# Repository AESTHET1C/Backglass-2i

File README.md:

# Backglass 2 Integrated Pinball Controller Board

This is the "integrated" version of the [Backglass 2 Pinball Controller Board](https://github.com/AESTHET1C/Backglass-2). The I/O has been changed from wire receptacles to a ribbon cable, and the ordering has changed to better suit wire management.

---

An Arduino Uno-compatible unified control board tailored to the Eli Whitney Museum 2019 summer pinball project.

The board contains the following hardware:

* Microchip ATmega8U2/16U2 (serial communication and code upload)
* Microchip ATmega328P (user code)
* Microchip ATmega48PB (audio/visual coprocessing)
* 4-character 7 segment display
* 2 analogue inputs (for reflectance sensors)
* 5 digital inputs (with integrated pull-ups)
* 3 current-limited LED outputs
* 1 PWM-controlled motor output
* 1 speaker output
* Micro USB interface
* 2.7 - 6.5 volt power input

All features of the board, with the exception of the motor, can be powered via USB.

-----

A user-oriented code library can be found here: <https://github.com/AESTHET1C/Backglass-2-Library/>

The coprocessor firmware can be found here: <https://github.com/AESTHET1C/Backglass-2-Firmware/>

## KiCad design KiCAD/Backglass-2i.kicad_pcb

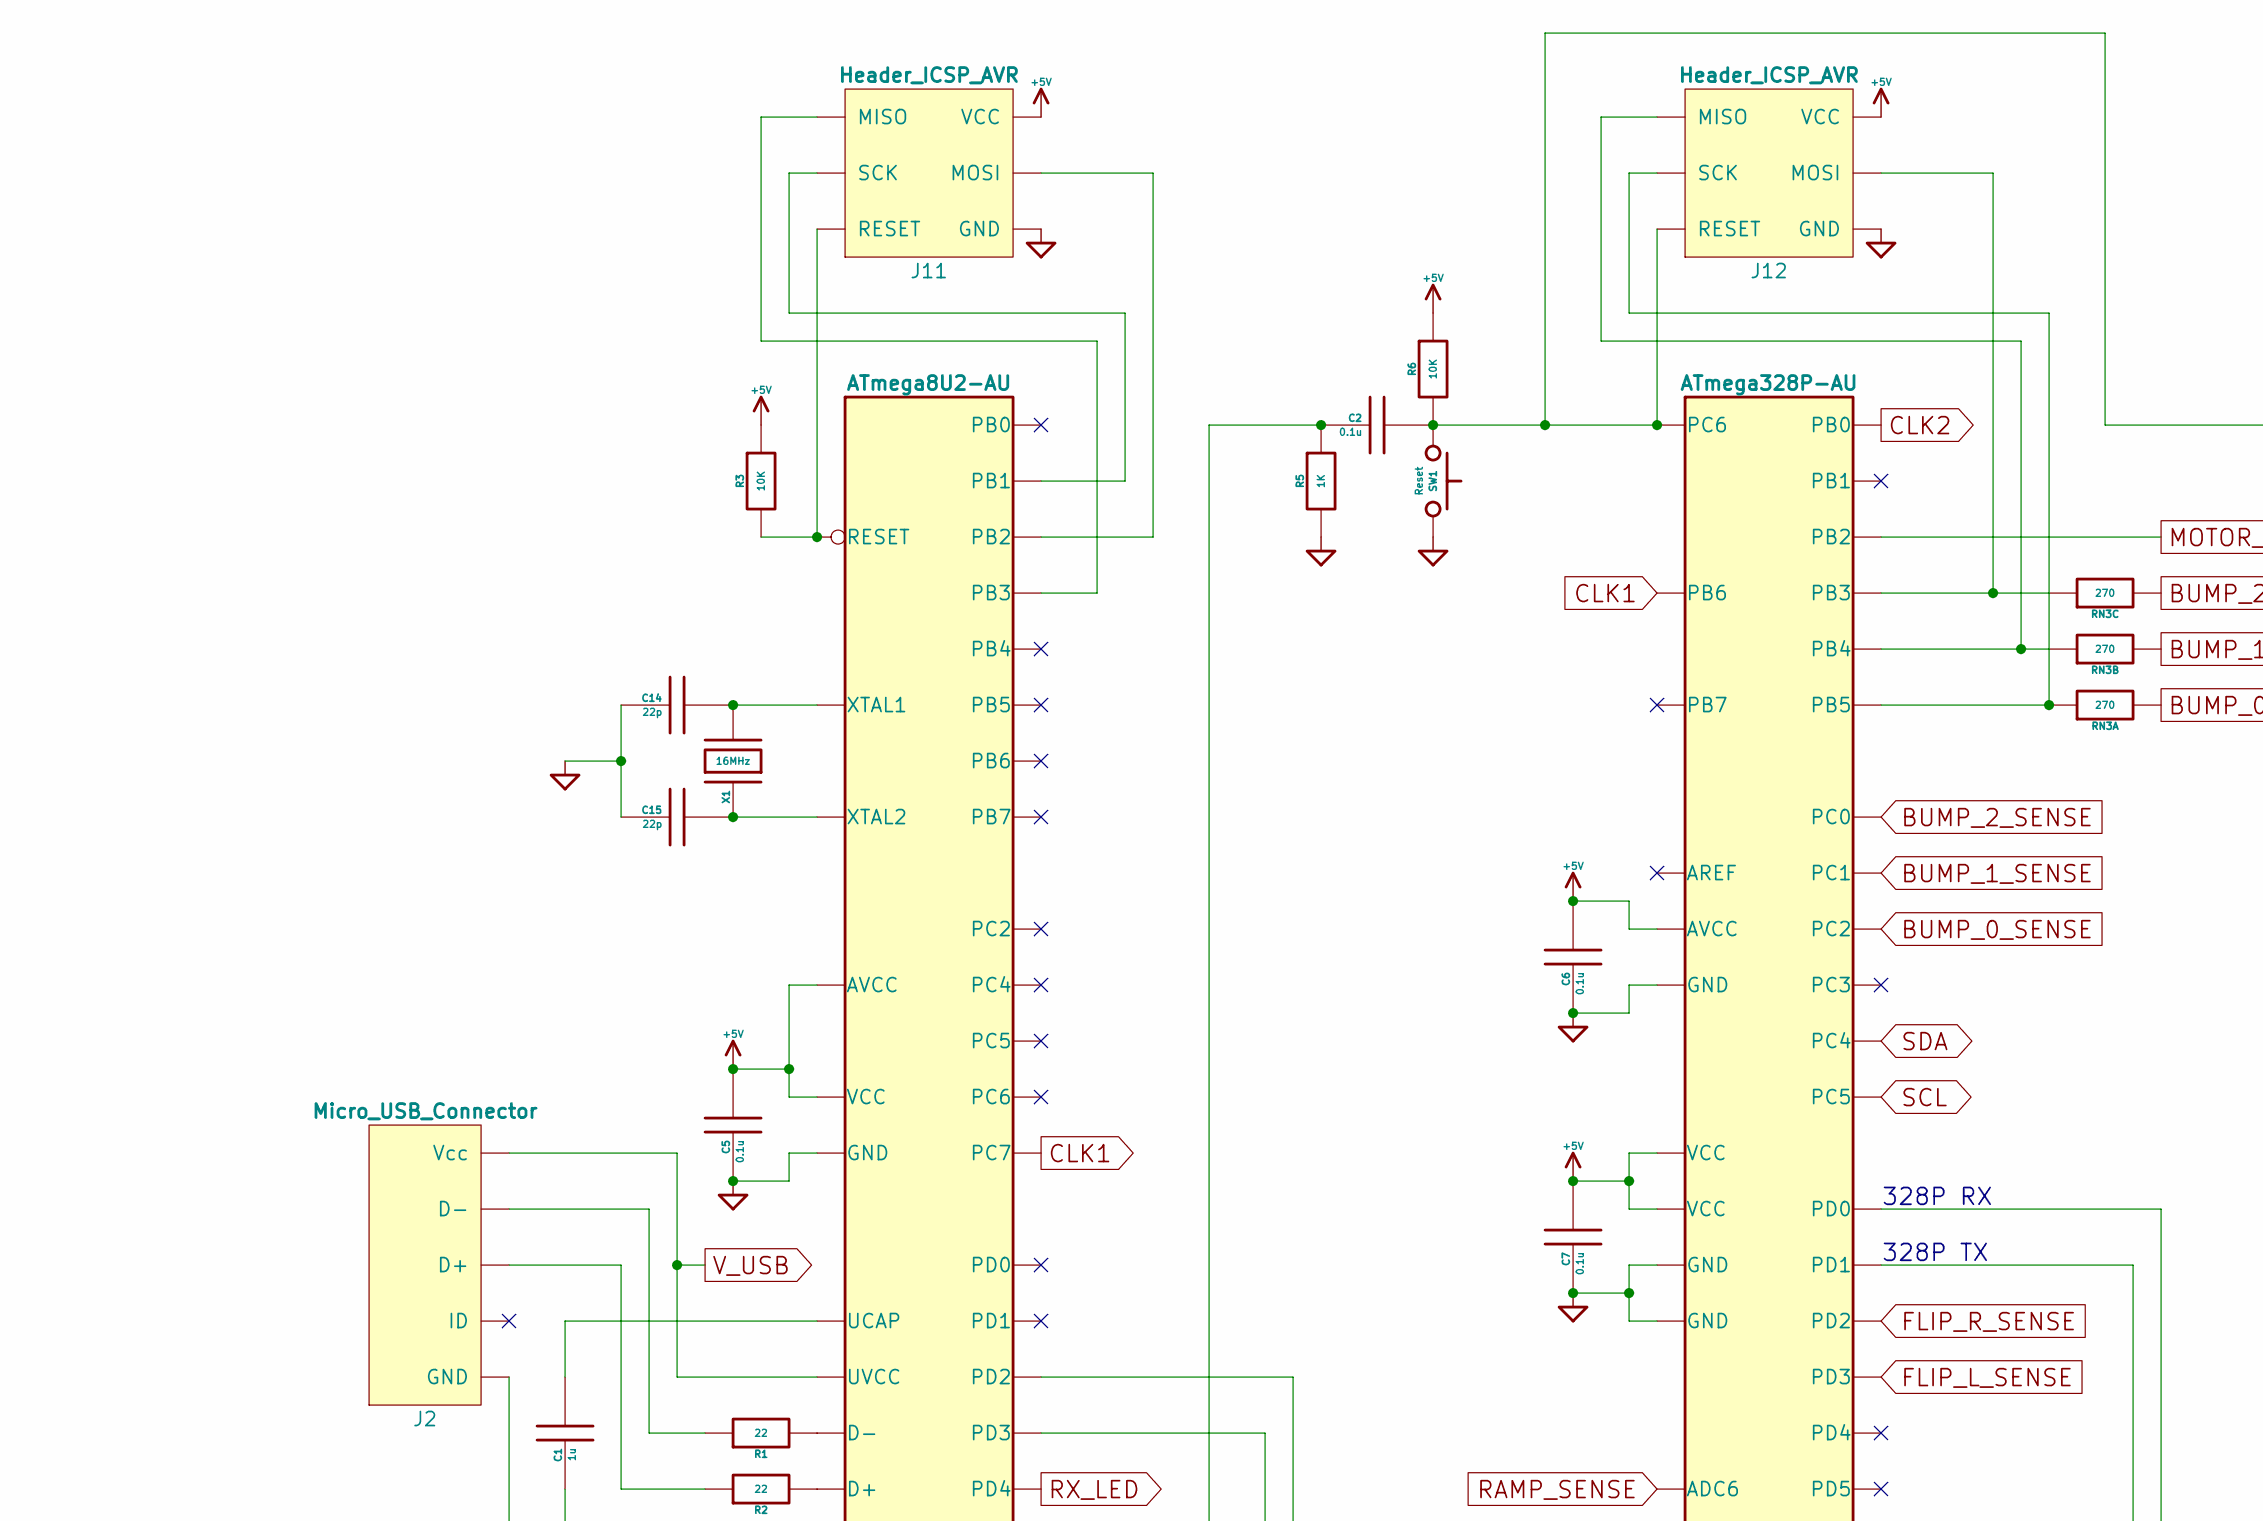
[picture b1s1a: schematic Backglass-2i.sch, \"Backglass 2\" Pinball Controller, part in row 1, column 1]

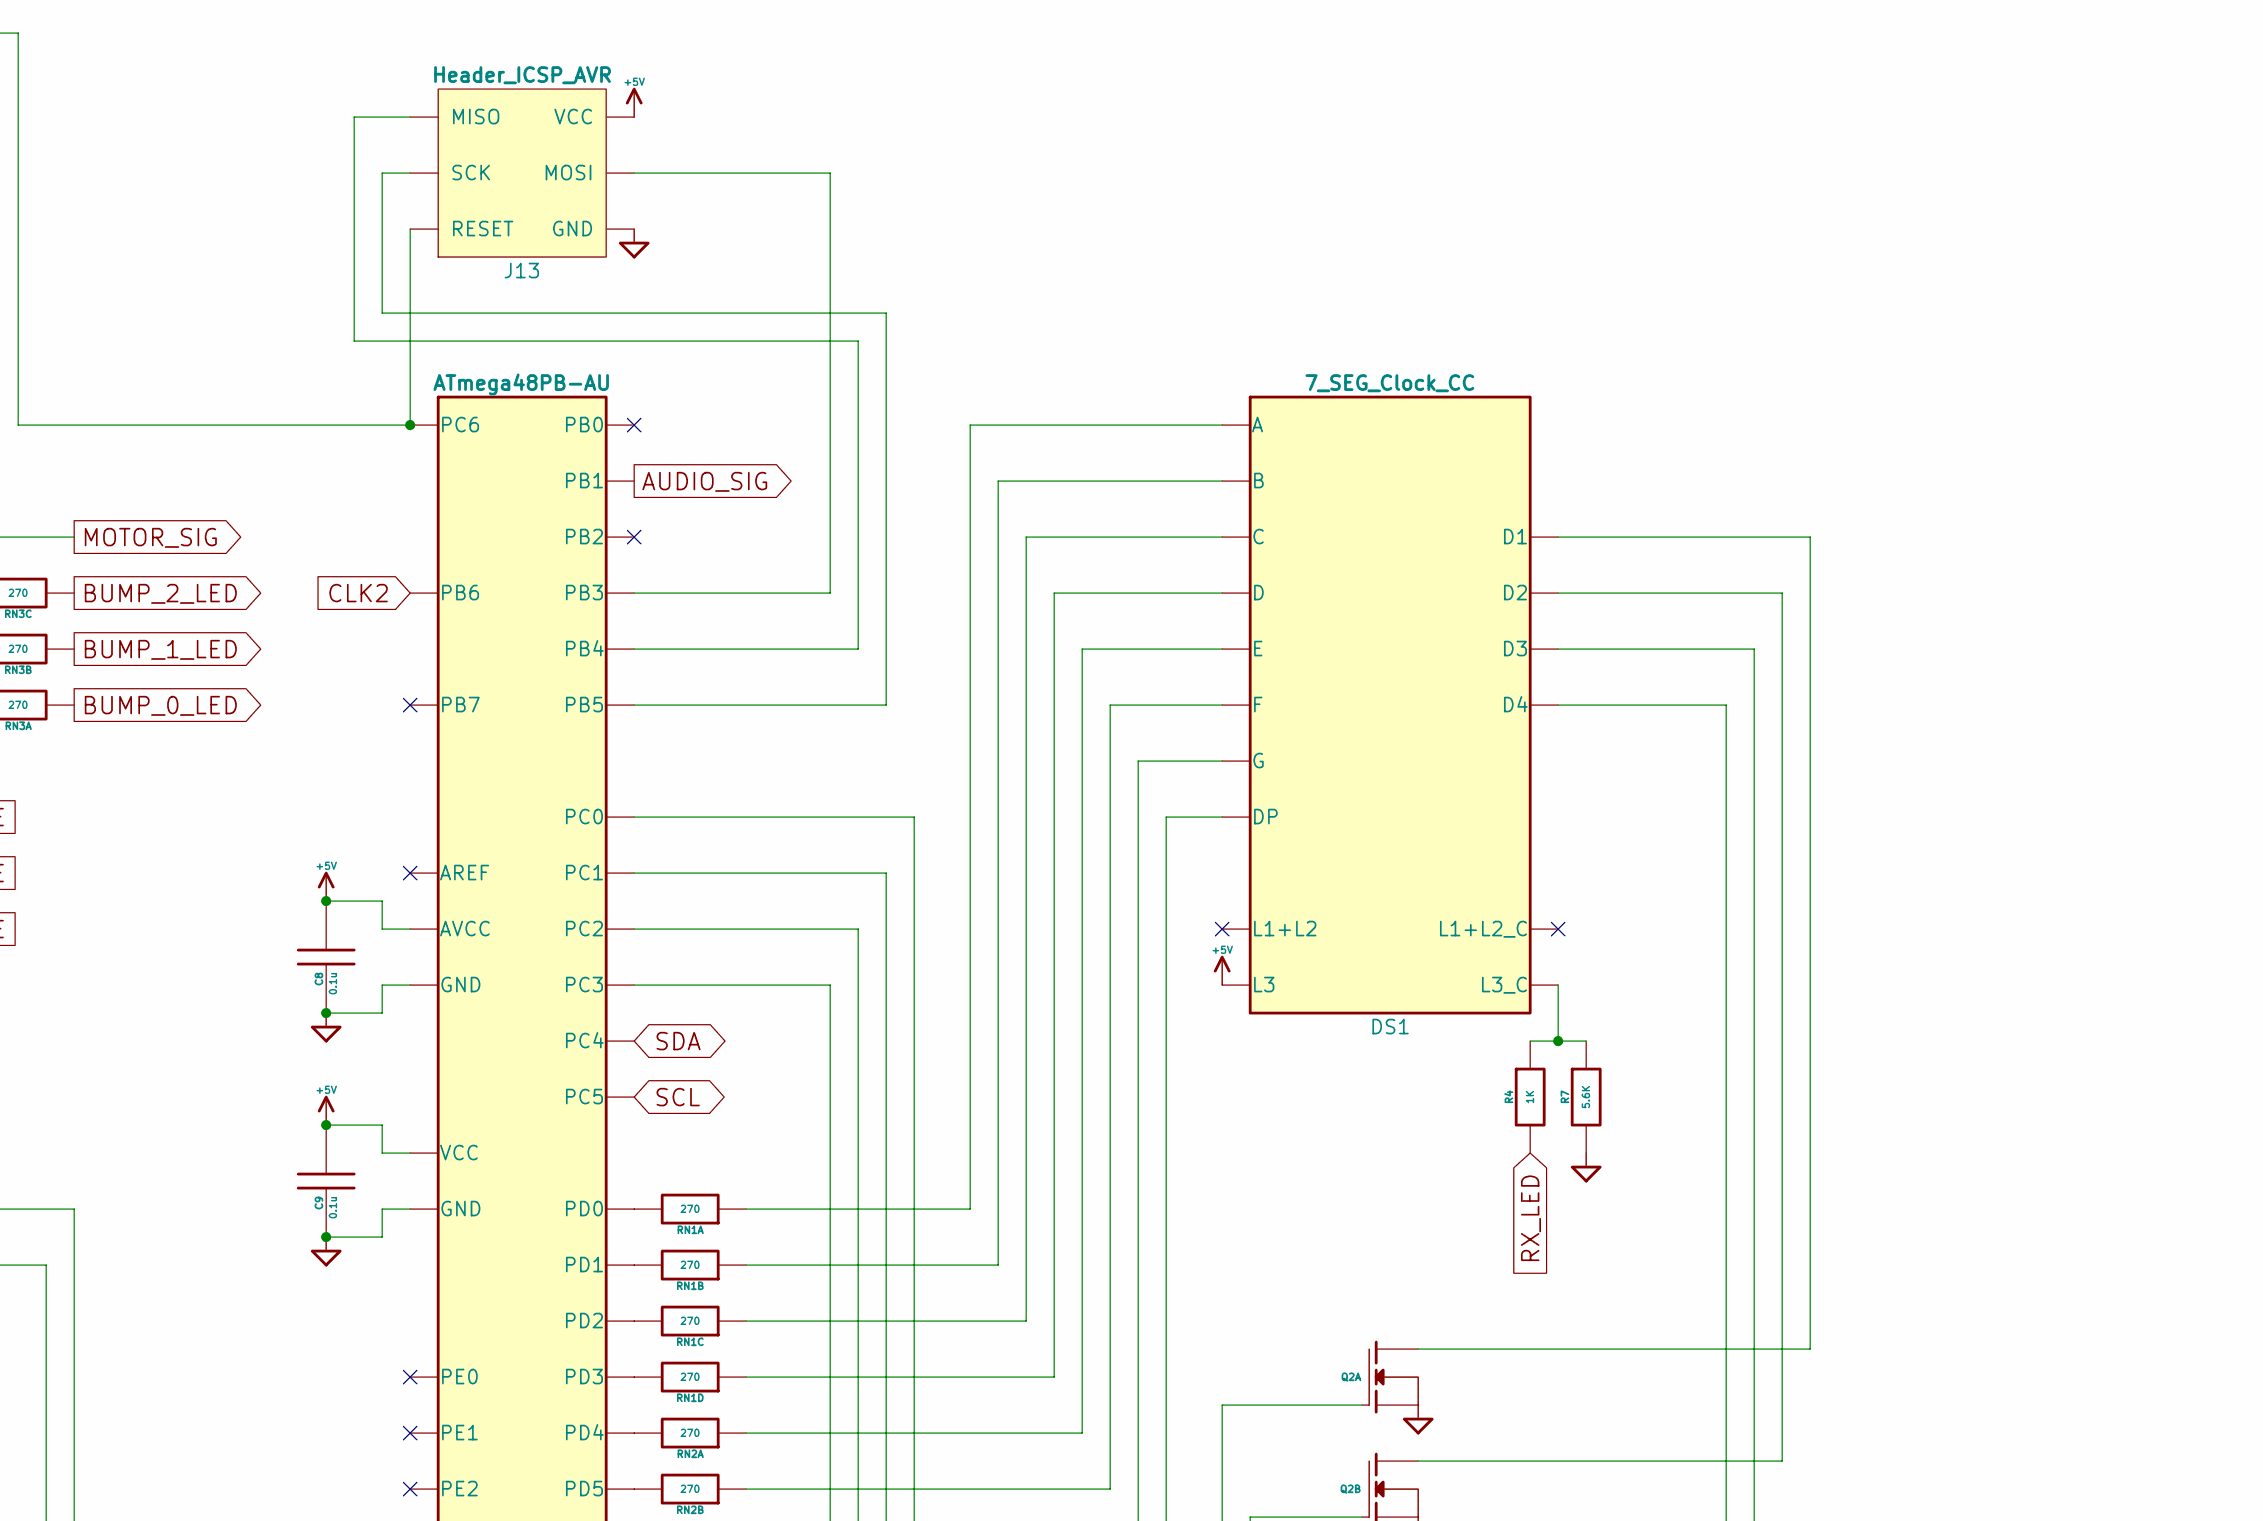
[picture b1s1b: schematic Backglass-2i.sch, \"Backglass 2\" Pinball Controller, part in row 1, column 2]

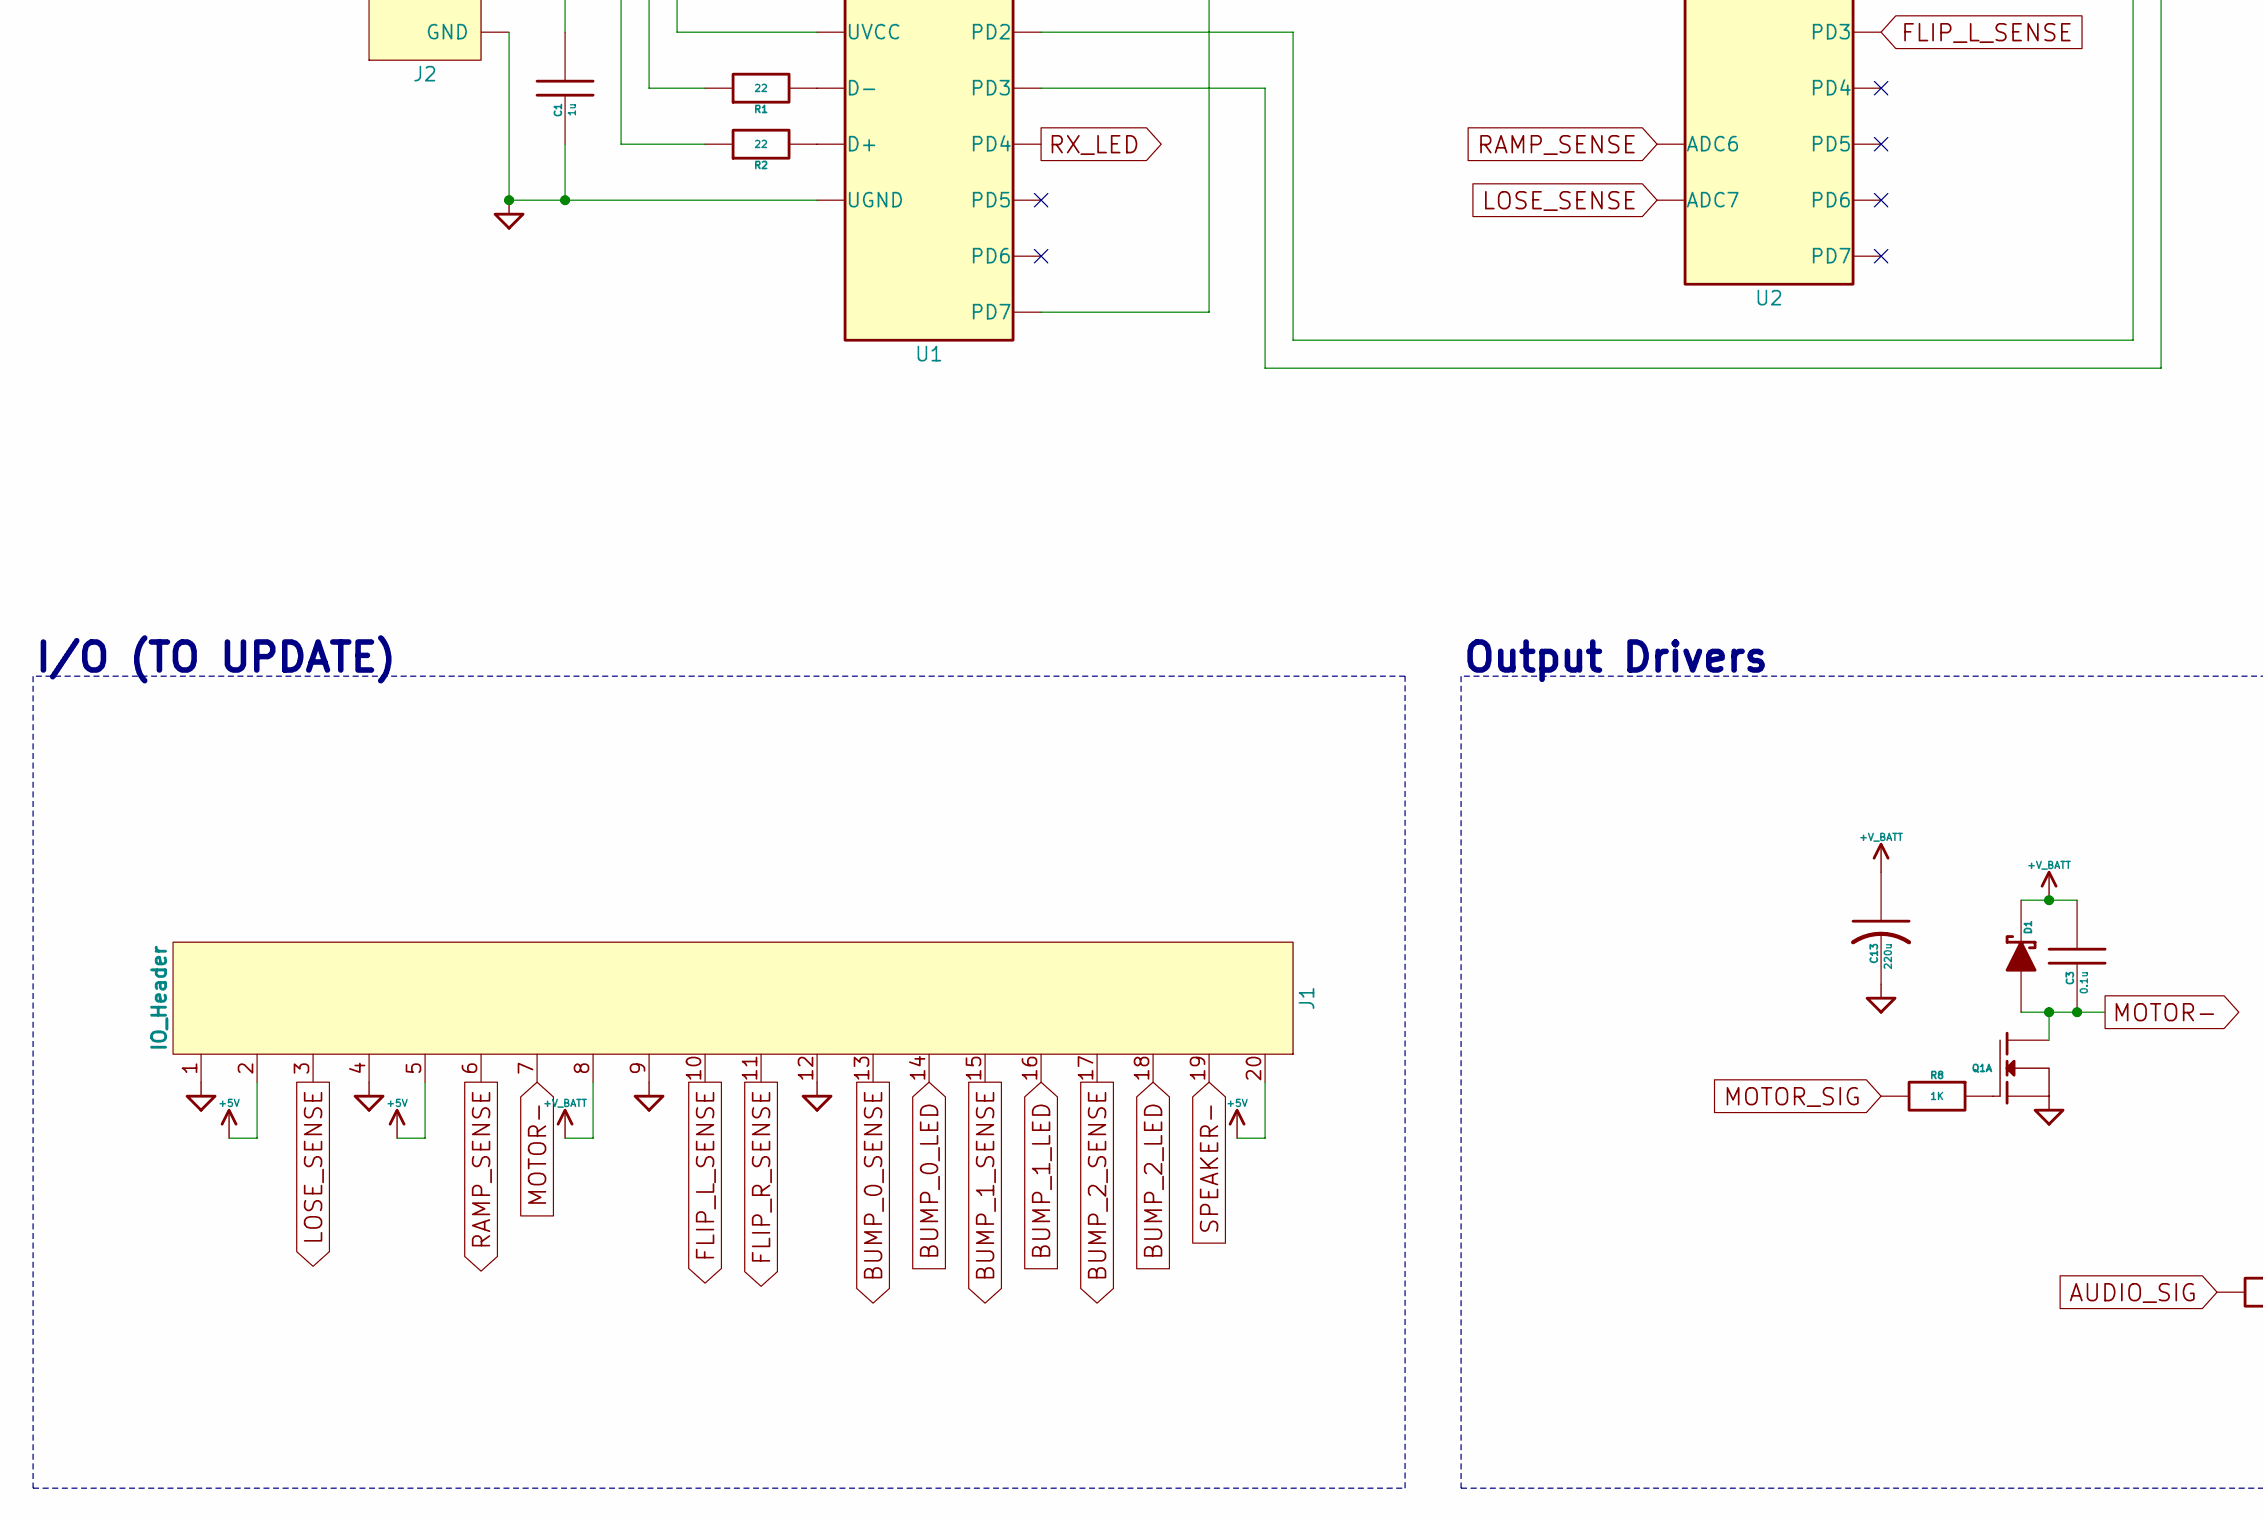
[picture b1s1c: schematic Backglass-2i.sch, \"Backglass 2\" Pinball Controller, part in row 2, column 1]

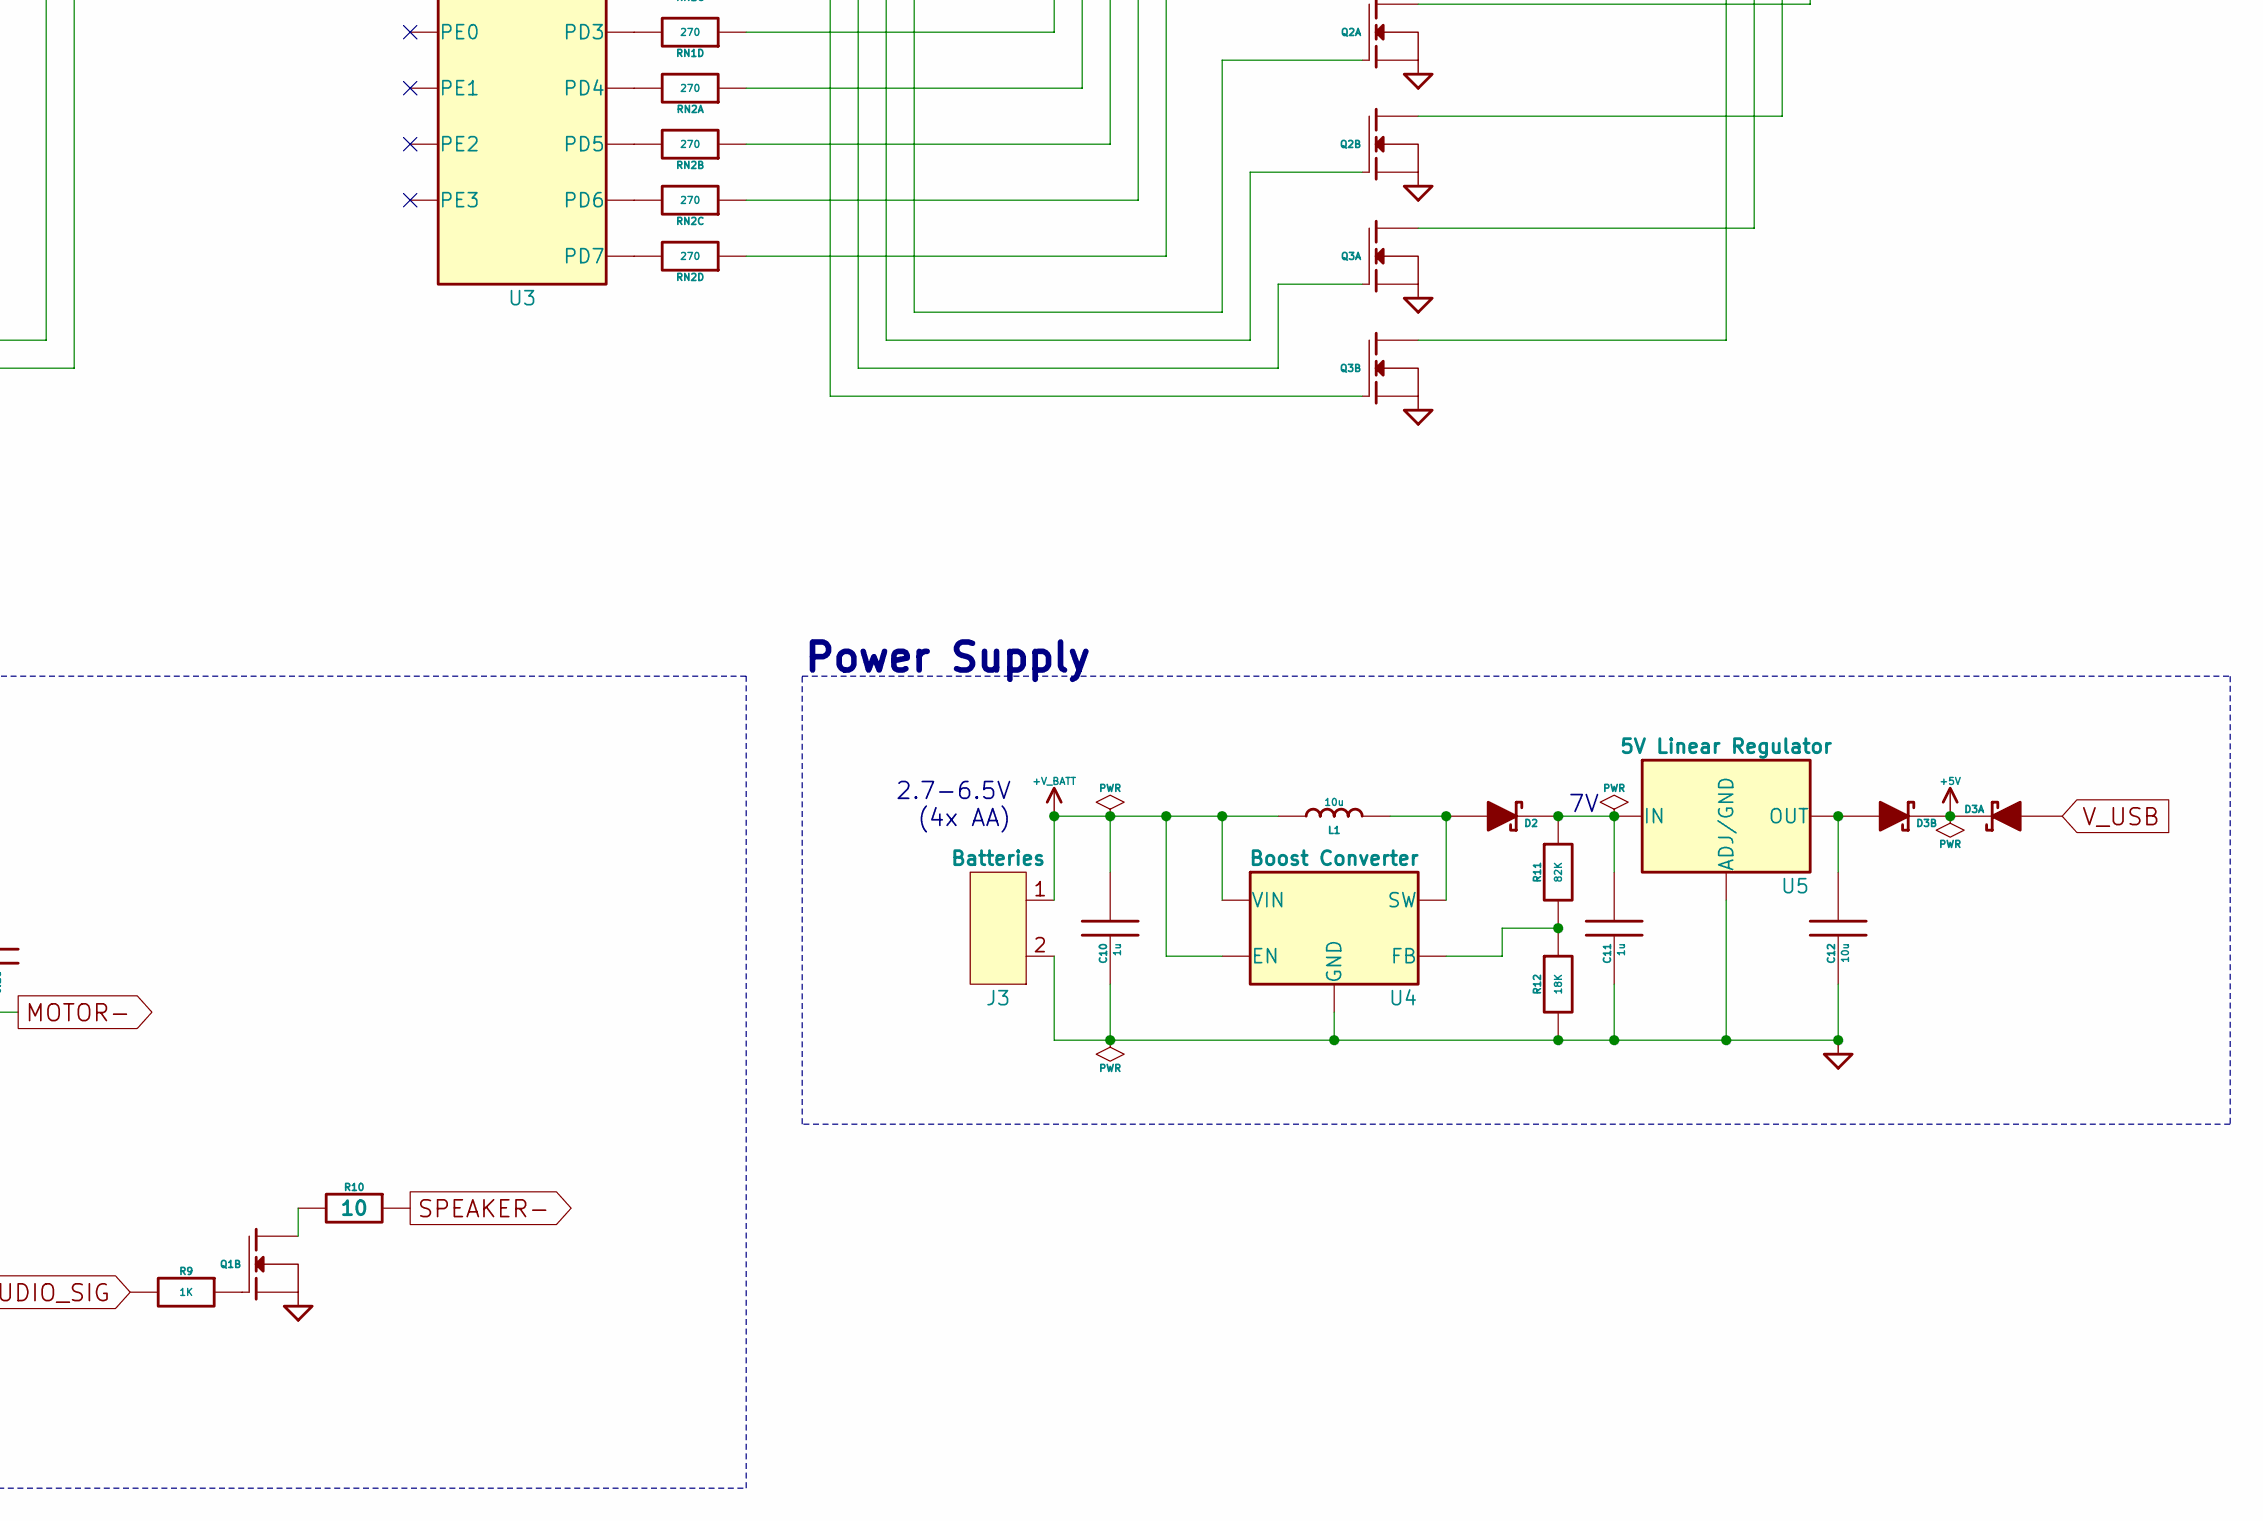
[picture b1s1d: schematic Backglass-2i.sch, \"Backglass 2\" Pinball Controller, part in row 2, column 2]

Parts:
C1, C10, C11: 1u; 1608
C2, C3, C5, C6, C7, C8, C9: 0.1u; 1608
C12: 10u; 2012
C13: 220u; C_6.3-2.5mm
C14, C15: 22p; 1608
D1, D2: D_Schottky; SOT-23-3_A-C
D3: D_Schottky_Dual_CC; SOT-23-3_AAC
DS1: 7_SEG_Clock_CC; TDCx10xxM
J1: IO_Header; TE_1-746610-5
J2: Micro_USB_Connector; Molex_1051640001
J3: Batteries; 2x1_0.1in
J11, J12, J13: Header_ICSP_AVR; AVR_ICSP_0.05in
L1: 10u; 3225
Q1: MOSFET_N_E_Dual; SOT-23-6_G1-S2-G2-D2-S1-D1
Q2, Q3: MOSFET_N_E_Dual; TSSOP-6_S1-G1-D2-S2-G2-D1
R1, R2: 22; 1608
R3, R6: 10K; 1608
R4, R5, R8, R9: 1K; 1608
R7: 5.6K; 1608
R10: 10; 3225
R11: 82K; 1608
R12: 18K; 1608
RN1, RN2, RN3: 270; Array_4x1608_Convex_NP
SW1: Reset; Tact_Switch_6mm
U1: ATmega8U2-AU; TQFP-32
U2: ATmega328P-AU; TQFP-32
U3: ATmega48PB-AU; TQFP-32
U4: Boost Converter; SOT-23-5
U5: 5V Linear Regulator; SOT-223-4
X1: 16MHz; 3.2x2.5_SMD_CRYSTAL

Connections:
+5V: C5.2, C6.2, C7.2, C8.2, C9.2, D3.C, DS1.9 (L3), J1.2, J1.5, J1.20, J11.2 (VCC), J12.2 (VCC), J13.2 (VCC), R3.1, R6.1, U1.4 (VCC), U1.32 (AVCC), U2.4 (VCC), U2.6 (VCC), U2.18 (AVCC), U3.4 (VCC), U3.18 (AVCC)
+V_BATT: C3.2, C10.2, C13.1, D1.C, J1.8, J3.1, L1.1, U4.4 (EN), U4.5 (VIN)
AUDIO_SIG: R9.2, U3.13 (PB1)
BUMP_0_LED: J1.14, RN3.8
BUMP_0_SENSE: J1.13, U2.25 (PC2)
BUMP_1_LED: J1.16, RN3.7
BUMP_1_SENSE: J1.15, U2.24 (PC1)
BUMP_2_LED: J1.18, RN3.6
BUMP_2_SENSE: J1.17, U2.23 (PC0)
CLK1: U1.22 (PC7), U2.7 (PB6)
CLK2: U2.12 (PB0), U3.7 (PB6)
FLIP_L_SENSE: J1.10, U2.1 (PD3)
FLIP_R_SENSE: J1.11, U2.32 (PD2)
GND: C1.1, C5.1, C6.1, C7.1, C8.1, C9.1, C10.1, C11.1, C12.1, C13.2, C14.1, C15.1, J1.1, J1.4, J1.9, J1.12, J2.5 (GND), J3.2, J11.6 (GND), J12.6 (GND), J13.6 (GND), Q1.S1, Q1.S2, Q2.S1, Q2.S2, Q3.S1, Q3.S2, R5.2, R7.2, R12.2, SW1.2 (NO), U1.3 (GND), U1.28 (UGND), U2.3 (GND), U2.5 (GND), U2.21 (GND), U3.5 (GND), U3.21 (GND), U4.2 (GND), U5.1 (ADJ/GND)
LOSE_SENSE: J1.3, U2.22 (ADC7)
MOTOR-: C3.1, D1.A, J1.7, Q1.D1
MOTOR_SIG: R8.2, U2.14 (PB2)
unnamed: C1.2, U1.27 (UCAP)
unnamed: C2.1, R5.1, U1.13 (PD7)
unnamed: C2.2, J12.5 (RESET), J13.5 (RESET), R6.2, SW1.1 (C), U2.29 (PC6), U3.29 (PC6)
unnamed: C11.2, D2.C, R11.1, U5.3 (IN)
unnamed: C12.2, D3.A2, U5.2 (OUT), U5.4
unnamed: C14.2, U1.1 (XTAL1), X1.2
unnamed: C15.2, U1.2 (XTAL2), X1.1
unnamed: D2.A, L1.2, U4.1 (SW)
unnamed: DS1.1 (D1), Q2.D1
unnamed: DS1.2 (D2), Q2.D2
unnamed: DS1.3 (D), RN1.4
unnamed: DS1.5 (E), RN2.1
unnamed: DS1.6 (D3), Q3.D1
unnamed: DS1.7 (DP), RN2.4
unnamed: DS1.8 (D4), Q3.D2
unnamed: DS1.10 (L3_C), R4.1, R7.1
unnamed: DS1.11 (F), RN2.2
unnamed: DS1.13 (C), RN1.3
unnamed: DS1.14 (A), RN1.1
unnamed: DS1.15 (G), RN2.3
unnamed: DS1.16 (B), RN1.2
unnamed: J2.2 (D-), R1.1
unnamed: J2.3 (D+), R2.1
unnamed: J11.1 (MISO), U1.17 (PB3)
unnamed: J11.3 (SCK), U1.15 (PB1)
unnamed: J11.4 (MOSI), U1.16 (PB2)
unnamed: J11.5 (RESET), R3.2, U1.24 (RESET)
unnamed: J12.1 (MISO), RN3.2, U2.16 (PB4)
unnamed: J12.3 (SCK), RN3.1, U2.17 (PB5)
unnamed: J12.4 (MOSI), RN3.3, U2.15 (PB3)
unnamed: J13.1 (MISO), U3.16 (PB4)
unnamed: J13.3 (SCK), U3.17 (PB5)
unnamed: J13.4 (MOSI), U3.15 (PB3)
unnamed: Q1.D2, R10.2
unnamed: Q1.G1, R8.1
unnamed: Q1.G2, R9.1
unnamed: Q2.G1, U3.23 (PC0)
unnamed: Q2.G2, U3.24 (PC1)
unnamed: Q3.G1, U3.25 (PC2)
unnamed: Q3.G2, U3.26 (PC3)
unnamed: R1.2, U1.30 (D-)
unnamed: R2.2, U1.29 (D+)
unnamed: R11.2, R12.1, U4.3 (FB)
unnamed: RN1.5, U3.1 (PD3)
unnamed: RN1.6, U3.32 (PD2)
unnamed: RN1.7, U3.31 (PD1)
unnamed: RN1.8, U3.30 (PD0)
unnamed: RN2.5, U3.11 (PD7)
unnamed: RN2.6, U3.10 (PD6)
unnamed: RN2.7, U3.9 (PD5)
unnamed: RN2.8, U3.2 (PD4)
unnamed: U1.8 (PD2), U2.31 (PD1)
unnamed: U1.9 (PD3), U2.30 (PD0)
RAMP_SENSE: J1.6, U2.19 (ADC6)
RX_LED: R4.2, U1.10 (PD4)
SCL: U2.28 (PC5), U3.28 (PC5)
SDA: U2.27 (PC4), U3.27 (PC4)
SPEAKER-: J1.19, R10.1
V_USB: D3.A1, J2.1 (Vcc), U1.31 (UVCC)

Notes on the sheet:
328P RX
328P TX
2.7-6.5V (4x AA)
Power Supply
I/O (TO UPDATE)
Output Drivers

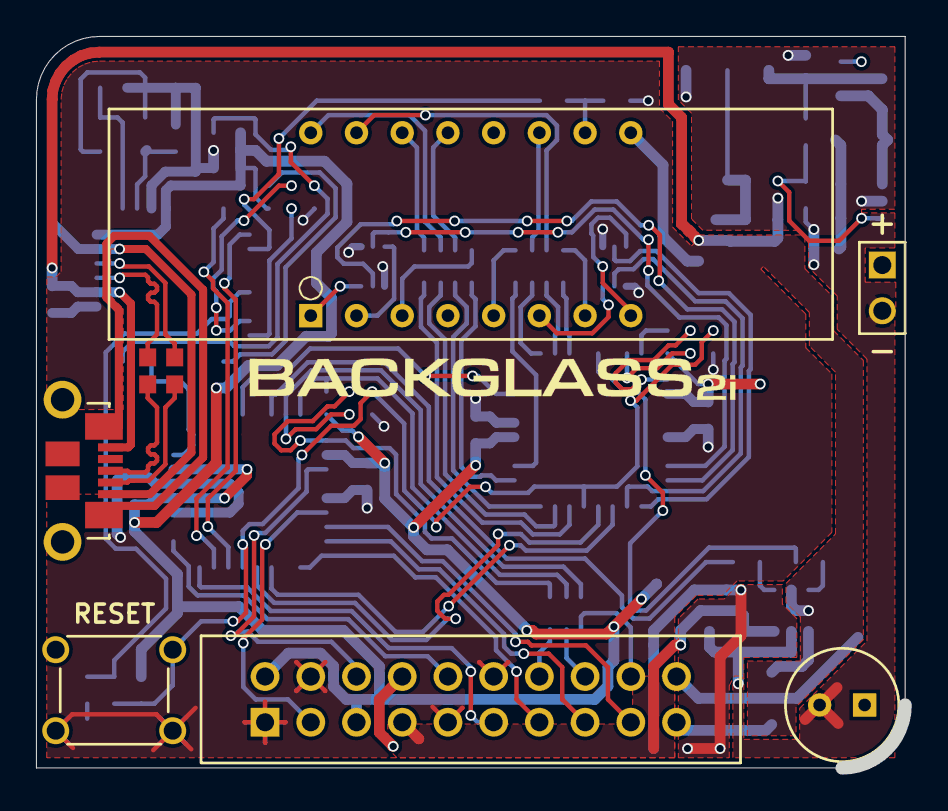
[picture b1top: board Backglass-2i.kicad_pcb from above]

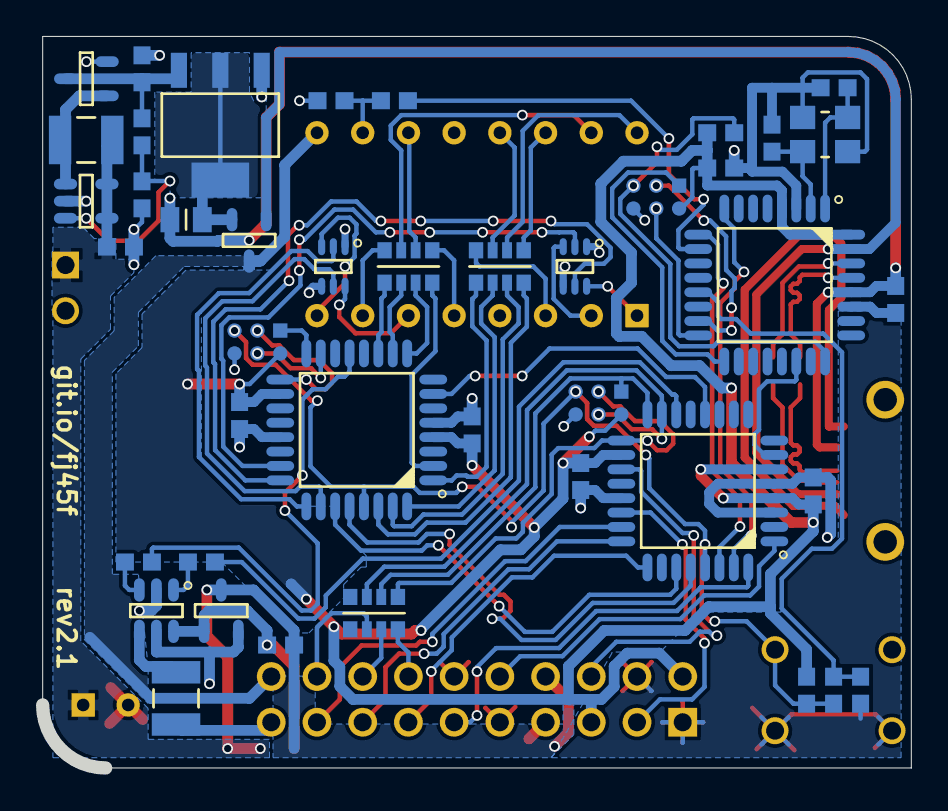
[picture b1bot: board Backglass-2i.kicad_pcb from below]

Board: 2 copper layers, 47.9 x 40.3 mm, 50 parts (42 on the bottom side), 76 nets.

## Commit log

2019-05-22 Real initial commit
    Copied files over from Backglass-2 repository.
2019-05-22 Minor versioning updates
    Changed Git.io link on silkscreen, updated version of schematic to 2.1, made note of changing I/O section.
2019-06-13 Updated layout
    Changed I/O connector and rerouted traces, removed I/O labels, updated logo
2019-06-13 Updated README
    Changed title and text to reflect the relationship to the Backglass 2 (non-i) board.
2019-06-13 Removed soldermask behind ICSP headers
